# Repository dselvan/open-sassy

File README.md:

# open-sassy
design and implementation of a slip angle sensor targeted for formula student electric controls applications

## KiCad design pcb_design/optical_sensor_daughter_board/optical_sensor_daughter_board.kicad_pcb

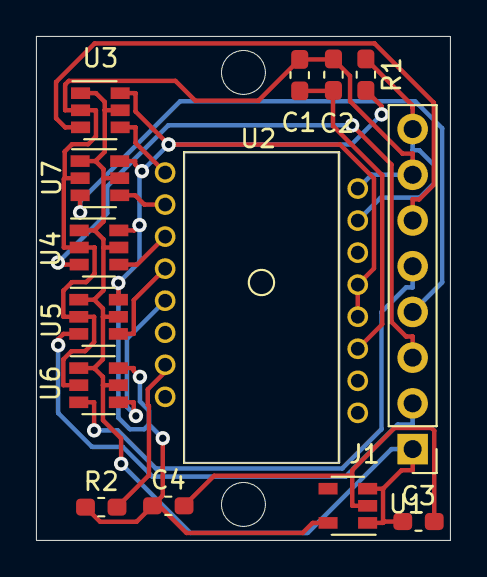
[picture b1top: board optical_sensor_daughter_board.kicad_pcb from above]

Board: 2 copper layers, 23.0 x 28.0 mm, 14 parts (0 on the bottom side), 17 nets.

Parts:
C1: 0.1uF; C_0603_1608Metric_Pad1.05x0.95mm_HandSolder
C2: 4.7uF; C_0603_1608Metric_Pad1.05x0.95mm_HandSolder
C3, C4: 1uF; C_0603_1608Metric_Pad1.05x0.95mm_HandSolder
J1: Conn_01x08_Male; PinHeader_1x08_P2.54mm_Vertical
R1: 10K; R_0603_1608Metric_Pad1.05x0.95mm_HandSolder
R2: 39; R_0603_1608Metric_Pad1.05x0.95mm_HandSolder
U1: TLV70019_SOT23-5; SOT-23-5
U2: PMW3360; PMW3389
U3, U4, U5, U6, U7: SN74LVC1T45DBV; SOT-23-6

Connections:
GND: C1.1, C2.1, J1.7, U2.8, U3.2, U4.2, U5.2, U6.2, U7.2
MISO: U2.12, U5.4
MISO_3.3V: J1.2, U5.3
MOIS_3.3V: J1.3, U4.3
MOSI: U2.11, U4.4
MOTION: U2.9, U3.4
MOTION_3.3V: J1.6, U3.3
unnamed: C1.2, C2.2, U2.3
unnamed: C3.2, C4.2, U1.2
unnamed: R2.2, U2.15
RESET: J1.8, R1.1, U2.7
SCLK: U2.10, U7.4
SLCK_3.3V: J1.4, U7.3
SS: U2.13, U6.4
SS_3.3V: J1.5, U6.3
VDD: C4.1, R1.2, R2.1, U1.5, U2.4, U2.5, U3.6, U4.6, U5.6, U6.6, U7.6
VIN: C3.1, J1.1, U1.1, U1.3, U3.1, U3.5, U4.1, U4.5, U5.1, U5.5, U6.1, U6.5, U7.1, U7.5

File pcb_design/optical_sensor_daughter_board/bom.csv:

"Source:","/home/deepak/projects/github.com/dselvan/open-sassy/pcb_design/optical_sensor_daughter_board/optical_sensor_daughter_board.sch"
"Date:","Wed 04 Sep 2019 05:53:41 PM BST"
"Tool:","Eeschema 5.1.4-e60b266~84~ubuntu18.04.1"
"Component Count:","14"
"Ref","Value","Footprint","Datasheet","Manufacturer","Vendor"
"C1","0.1uF","Capacitor_SMD:C_0603_1608Metric_Pad1.05x0.95mm_HandSolder","~","",""
"C2","4.7uF","Capacitor_SMD:C_0603_1608Metric_Pad1.05x0.95mm_HandSolder","~","",""
"C3","1uF","Capacitor_SMD:C_0603_1608Metric_Pad1.05x0.95mm_HandSolder","~","",""
"C4","1uF","Capacitor_SMD:C_0603_1608Metric_Pad1.05x0.95mm_HandSolder","~","",""
"J1","Conn_01x08_Male","Connector_PinHeader_2.54mm:PinHeader_1x08_P2.54mm_Vertical","~","",""
"R1","10K","Resistor_SMD:R_0603_1608Metric_Pad1.05x0.95mm_HandSolder","~","",""
"R2","39","Resistor_SMD:R_0603_1608Metric_Pad1.05x0.95mm_HandSolder","~","",""
"U1","TLV70019_SOT23-5","Package_TO_SOT_SMD:SOT-23-5","http://www.ti.com/lit/ds/symlink/tlv700.pdf","",""
"U2","PMW3360","pmw3389:PMW3389","","",""
"U3","SN74LVC1T45DBV","Package_TO_SOT_SMD:SOT-23-6","http://www.ti.com/lit/ds/symlink/sn74lvc1t45.pdf","",""
"U4","SN74LVC1T45DBV","Package_TO_SOT_SMD:SOT-23-6","http://www.ti.com/lit/ds/symlink/sn74lvc1t45.pdf","",""
"U5","SN74LVC1T45DBV","Package_TO_SOT_SMD:SOT-23-6","http://www.ti.com/lit/ds/symlink/sn74lvc1t45.pdf","",""
"U6","SN74LVC1T45DBV","Package_TO_SOT_SMD:SOT-23-6","http://www.ti.com/lit/ds/symlink/sn74lvc1t45.pdf","",""
"U7","SN74LVC1T45DBV","Package_TO_SOT_SMD:SOT-23-6","http://www.ti.com/lit/ds/symlink/sn74lvc1t45.pdf","",""

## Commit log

2019-03-03 add docs folder for github pages support
2019-03-03 Set theme jekyll-theme-minimal
2019-05-12 Set theme jekyll-theme-slate
2019-05-12 Create notes.md
    Add link for arduino documentation generation
2019-06-20 Add inital pcb design for optical sensor daughter board
2019-06-20 Add submodule for storing uni research
2019-06-20 Update submodule settings
2019-06-26 Working commit that needs to be refeactored
2019-08-03 Initial code to read from optical sensor based on mrjohnk's code
2019-08-03 Update CPI settings and add lift cutoff setting
2019-08-03 Update submodule to point to my fork
2019-08-03 Disable lift cutoff?
2019-08-05 Add simple threading lib
2019-08-09 Add unit tests for SignalProcessing class
2019-08-15 working commit
2019-08-20 sensor capture
2019-08-20 octave script for img and plots
2019-08-23 wip calc slip angle
2019-09-04 WIP daughter board
2019-09-05 New 0x08 firmware added
